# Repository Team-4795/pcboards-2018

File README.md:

# pcboards-2018
Printed Circuit Board designs and experiments, 2018

Create each design project in its own folder

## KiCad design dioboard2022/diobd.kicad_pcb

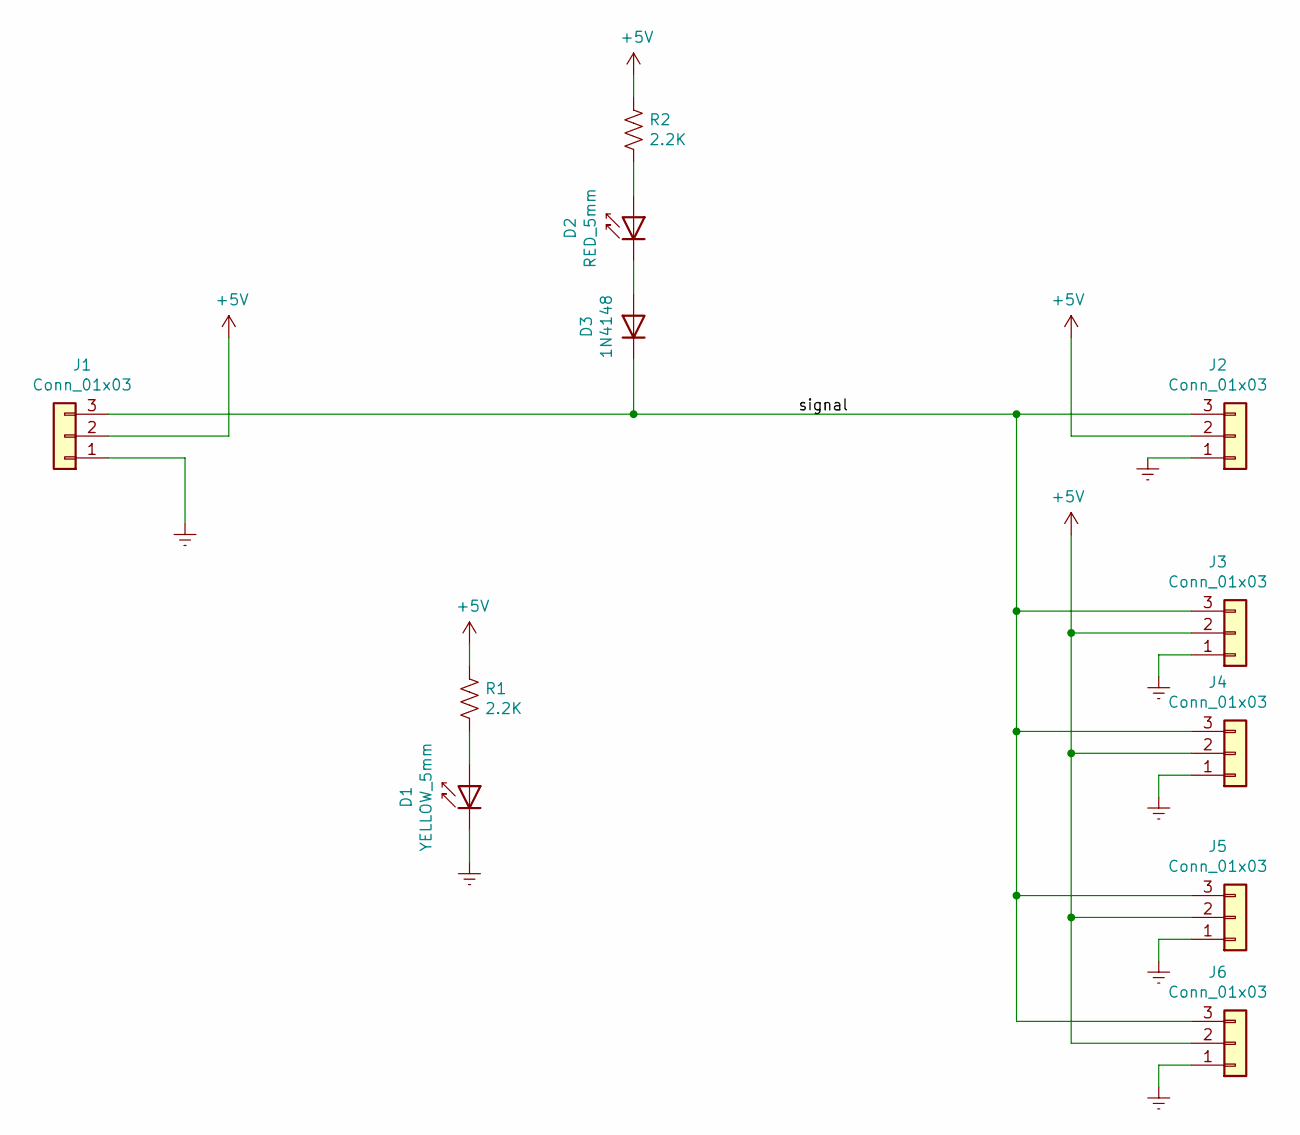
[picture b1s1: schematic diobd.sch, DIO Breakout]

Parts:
D1: YELLOW_5mm; LED_D5.0mm
D2: RED_5mm; LED_D5.0mm
D3: 1N4148; D_DO-35_SOD27_P7.62mm_Horizontal
J1: Conn_01x03; PinSocket_1x03_P2.54mm_Horizontal
J2: Conn_01x03; PinHeader_1x03_P2.54mm_Horizontal
J3, J4, J5, J6: Conn_01x03; PinHeader_1x03_P2.54mm_Vertical
R1, R2: 2.2K; R_Axial_DIN0207_L6.3mm_D2.5mm_P10.16mm_Horizontal

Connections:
+5V: J1.2, J2.2, J3.2, J4.2, J5.2, J6.2, R1.1, R2.1
/signal: D3.1 (K), J1.3, J2.3, J3.3, J4.3, J5.3, J6.3
Earth: D1.1 (K), J1.1, J2.1, J3.1, J4.1, J5.1, J6.1
unnamed: D1.2 (A), R1.2
unnamed: D2.1 (K), D3.2 (A)
unnamed: D2.2 (A), R2.2

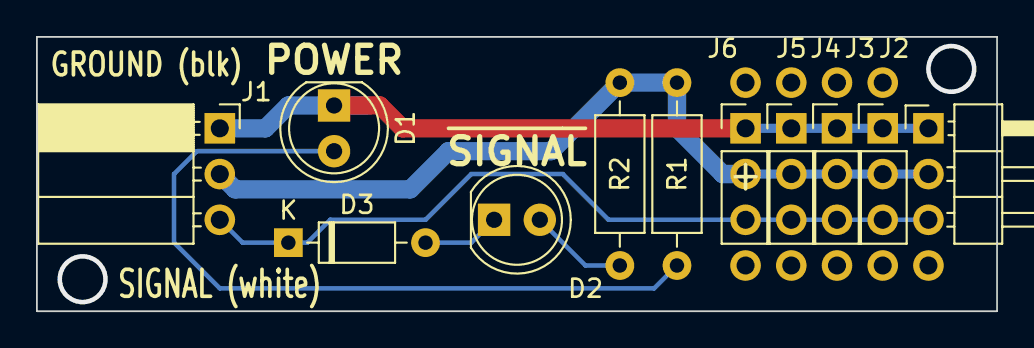
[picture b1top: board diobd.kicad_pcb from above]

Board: 2 copper layers, 53.3 x 15.2 mm, 11 parts (0 on the bottom side), 6 nets.

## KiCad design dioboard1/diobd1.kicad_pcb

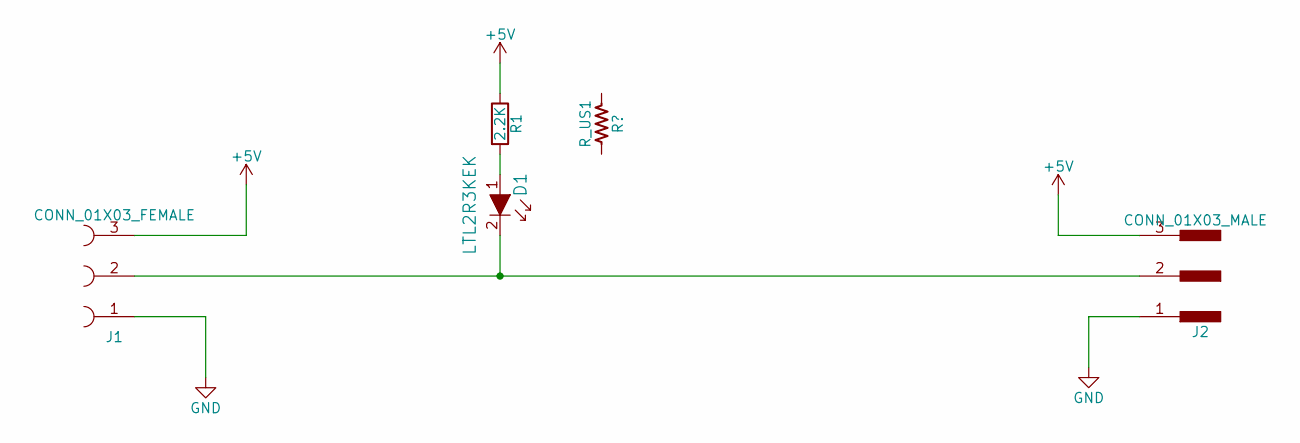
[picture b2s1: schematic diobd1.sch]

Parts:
D1: LTL2R3KEK; LED_D5.0mm; MPN LTL2R3KEK; Digi-Key_PN 160-1682-ND
J1: CONN_01X03_FEMALE; Socket_Strip_Angled_1x03_Pitch2.54mm
J2: CONN_01X03_MALE; Pin_Header_Angled_1x03_Pitch2.54mm
R1: 2.2K; R_Axial_DIN0207_L6.3mm_D2.5mm_P10.16mm_Horizontal

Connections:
+5V: J1.3, J2.3, R1.1
GND: J1.1, J2.1
unnamed: D1.1, R1.2
unnamed: D1.2, J1.2, J2.2

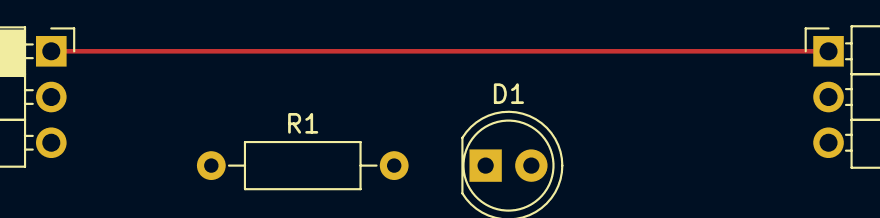
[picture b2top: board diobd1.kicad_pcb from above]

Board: 2 copper layers, 4 parts (0 on the bottom side), 4 nets.

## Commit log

2018-10-26 start on first board: just connectors and a few wires
2018-11-02 schematic edits. use power symbols. add one LED circuit library for our own symbols
2018-11-02 redraw with KiCad 5.0.1
2018-11-08 copy the board to experiment with the next steps, so I can write it up on the wiki. trial board layout too
2018-11-15 dummy file for everyone to edit
2018-11-15 a better name to encourage team members to edit it
2018-11-15 Edited the prompt for other team members to add their line to this file
2018-11-16 Added line with name
2018-11-16 Resolve Merge Error
2018-11-16 made pcb more compact
2018-11-16 Finished preliminary routing
2018-11-16 added silkscreen
2018-11-17 Another name on the file
2018-11-22 simple schematic for use on led circuit tutorial page
2018-12-19 fakerio1: simple digital input portion of a fake robot controller for testing switches and sensors. Just a schematic so far.
2019-01-18 move some labels on the assembly-drawing layer, add lines on fab layer pointing to parts from labels that are outside the board outline.
2019-01-22 2019 build season changes add year to back silk add signal/pin name text to front silk squeeze in two mounting holes
2019-01-22 adjust mounting hole position to try for round coordinate numbers easier to use
2019-02-15 schematic of our 12-24v passive POE test circuit
2019-02-22 mosfet inverter and gate schematic
2019-02-25 created inverter board
2019-02-25 fixed MOSFET polarity
2019-02-25 added pulldown resistors
2022-02-26 2022 dio test board, with proto area
2023-01-12 belatedly add banner engineering sensor adaptor design developed in 2022
2023-02-10 branch dioboard2 (2019) into dioboard2023\ update year improve silkscreen labels a bit
